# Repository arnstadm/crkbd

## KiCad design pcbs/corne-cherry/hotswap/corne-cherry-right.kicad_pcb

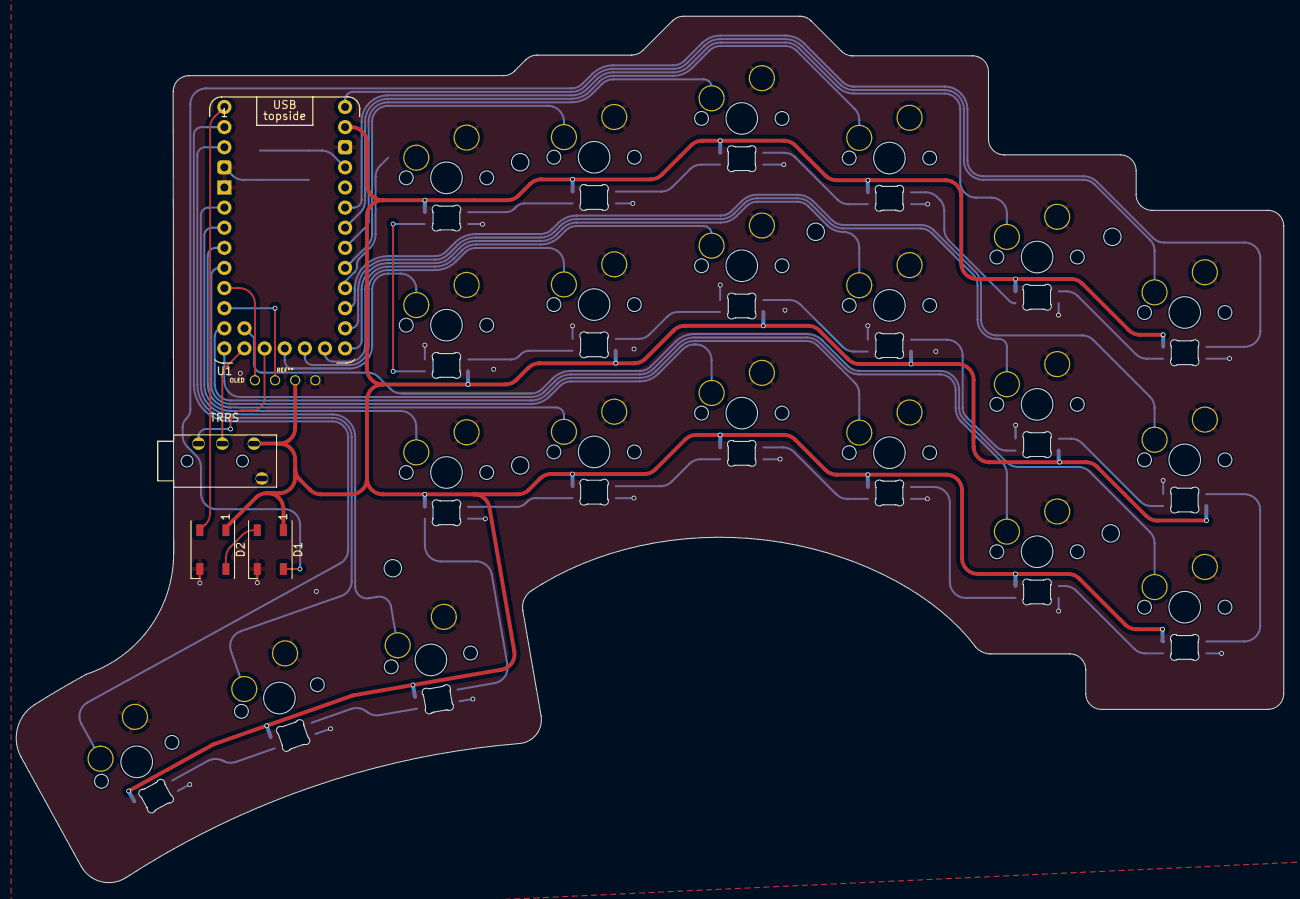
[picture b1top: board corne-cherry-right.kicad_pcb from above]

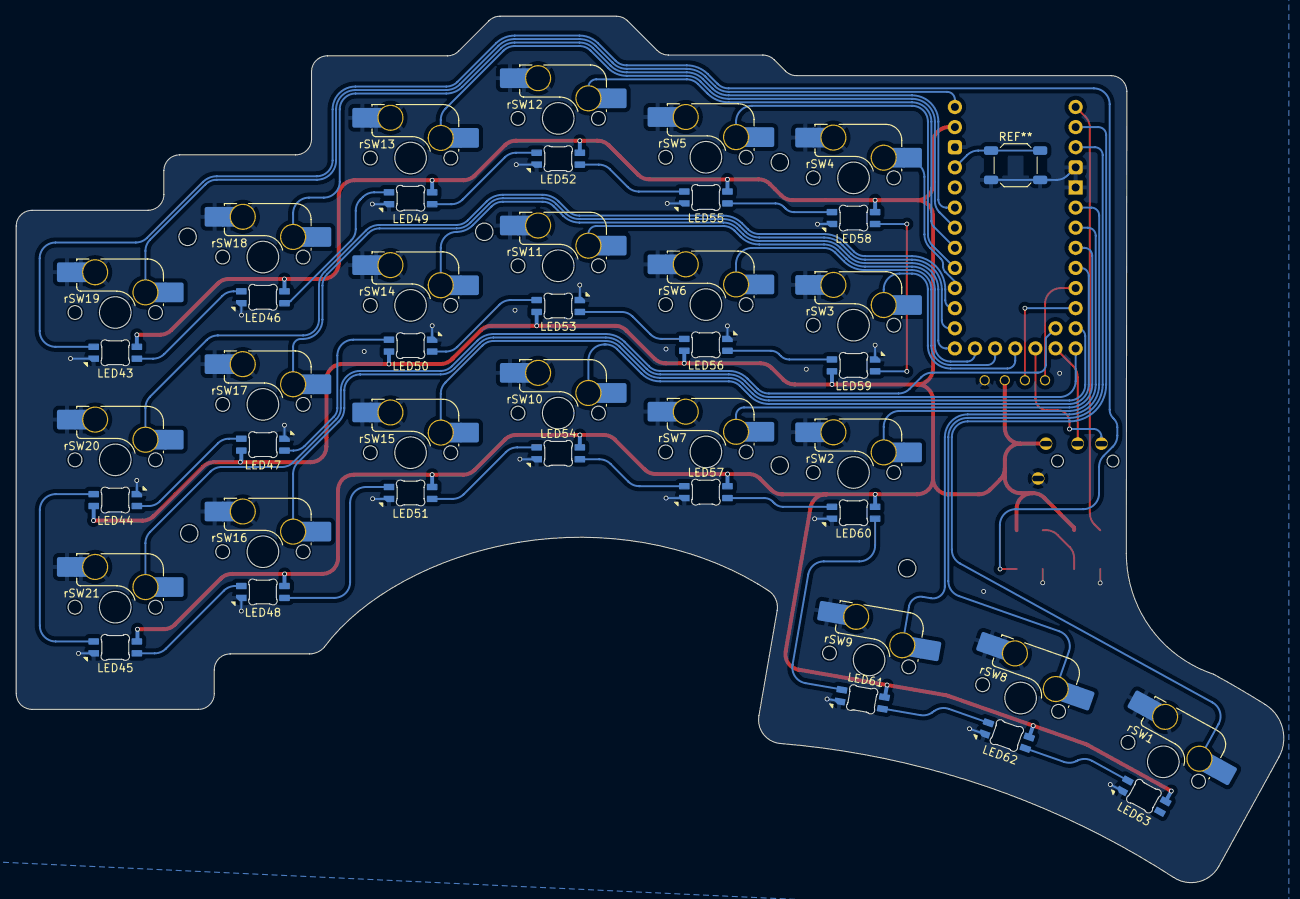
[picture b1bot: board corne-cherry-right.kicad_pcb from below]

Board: 2 copper layers, 160.0 x 109.4 mm, 47 parts (42 on the bottom side), 50 nets.

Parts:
D1, D2: WS2812B; LED_WS2812B_PLCC4_5.0x5.0mm_P3.2mm
LED43, LED45, LED46, LED48, LED49, LED51, LED52, LED54, LED55, LED57, LED58, LED60, LED61, LED62, LED63: MX_SK6812MINI-E; LED_MX_6028R
LED44, LED47, LED50, LED53, LED56, LED59: MX_SK6812MINI-E; LED_MX_6028R-ROT
TRRS: PJ-320A
U1: rp2040; rp2040promicro
rJ3: Conn_01x04; OLED
rSW1, rSW2, rSW3, rSW4, rSW5, rSW6, rSW7, rSW8, rSW9, rSW10, rSW11, rSW12, rSW13, rSW14, rSW15, rSW16, rSW17, rSW18, rSW19, rSW20, rSW21: SW_Push; SW_MX_HS_CPG151101S11_1u

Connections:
+5VR: D1.1 (VDD), D2.1 (VDD), LED43.1 (VDD), LED44.1 (VDD), LED45.1 (VDD), LED46.1 (VDD), LED47.1 (VDD), LED48.1 (VDD), LED49.1 (VDD), LED50.1 (VDD), LED51.1 (VDD), LED52.1 (VDD), LED53.1 (VDD), LED54.1 (VDD), LED55.1 (VDD), LED56.1 (VDD), LED57.1 (VDD), LED58.1 (VDD), LED59.1 (VDD), LED60.1 (VDD), LED61.1 (VDD), LED62.1 (VDD), LED63.1 (VDD), TRRS.2, U1.5V, rJ3.3
/right/KEY1: U1.0 (GP0), rSW1.1
/right/KEY2: U1.3 (GP3), rSW2.1
/right/KEY3: U1.14 (GP14), rSW3.1
/right/KEY4: U1.22 (GP22), rSW4.1
/right/KEY5: U1.26 (GP26), rSW5.1
/right/KEY6: U1.15 (GP15), rSW6.1
/right/KEY7: U1.4 (GP4), rSW7.1
/right/KEY8: U1.1 (GP1), rSW8.1
/right/KEY9: U1.2 (GP2), rSW9.1
/right/KEY10: U1.5 (GP5), rSW10.1
/right/KEY11: U1.16 (GP16), rSW11.1
/right/KEY12: U1.27 (GP27), rSW12.1
/right/KEY13: U1.28 (GP28), rSW13.1
/right/KEY14: U1.21 (GP21), rSW14.1
/right/KEY15: U1.8 (GP8), rSW15.1
/right/KEY16: U1.9 (GP9), rSW16.1
/right/KEY17: U1.23 (GP23), rSW17.1
/right/KEY18: U1.29 (GP29), rSW18.1
/right/KEY19: U1.11 (GP11), rSW19.1
/right/KEY20: U1.20 (GP20), rSW20.1
/right/KEY21: U1.25 (GP25), rSW21.1
/right/LED: D2.2 (DOUT), U1.10 (GP10)
/right/RX: TRRS.4, U1.13 (GP13)
/right/SCL: U1.7 (GP7), rJ3.2
/right/SDA: U1.6 (GP6), rJ3.1
/right/TX: TRRS.3, U1.12 (GP12)
GNDR: D1.3 (VSS), D2.3 (VSS), LED43.4 (VSS), LED44.4 (VSS), LED45.4 (VSS), LED46.4 (VSS), LED47.4 (VSS), LED48.4 (VSS), LED49.4 (VSS), LED50.4 (VSS), LED51.4 (VSS), LED52.4 (VSS), LED53.4 (VSS), LED54.4 (VSS), LED55.4 (VSS), LED56.4 (VSS), LED57.4 (VSS), LED58.4 (VSS), LED59.4 (VSS), LED60.4 (VSS), LED61.4 (VSS), LED62.4 (VSS), LED63.4 (VSS), TRRS.1, U1.G (GND), rJ3.4, rSW1.2, rSW2.2, rSW3.2, rSW4.2, rSW5.2, rSW6.2, rSW7.2, rSW8.2, rSW9.2, rSW10.2, rSW11.2, rSW12.2, rSW13.2, rSW14.2, rSW15.2, rSW16.2, rSW17.2, rSW18.2, rSW19.2, rSW20.2, rSW21.2
unnamed: D1.4 (DIN), LED43.3 (DIN)
unnamed: D1.2 (DOUT), D2.4 (DIN)
unnamed: LED43.2 (DOUT), LED46.3 (DIN)
unnamed: LED44.3 (DIN), LED47.2 (DOUT)
unnamed: LED44.2 (DOUT), LED45.3 (DIN)
unnamed: LED45.2 (DOUT), LED48.3 (DIN)
unnamed: LED46.2 (DOUT), LED49.3 (DIN)
unnamed: LED47.3 (DIN), LED50.2 (DOUT)
unnamed: LED48.2 (DOUT), LED51.3 (DIN)
unnamed: LED49.2 (DOUT), LED52.3 (DIN)
unnamed: LED50.3 (DIN), LED53.2 (DOUT)
unnamed: LED51.2 (DOUT), LED54.3 (DIN)
unnamed: LED52.2 (DOUT), LED55.3 (DIN)
unnamed: LED53.3 (DIN), LED56.2 (DOUT)
unnamed: LED54.2 (DOUT), LED57.3 (DIN)
unnamed: LED55.2 (DOUT), LED58.3 (DIN)
unnamed: LED56.3 (DIN), LED59.2 (DOUT)
unnamed: LED57.2 (DOUT), LED60.3 (DIN)
unnamed: LED58.2 (DOUT), LED59.3 (DIN)
unnamed: LED60.2 (DOUT), LED61.3 (DIN)
unnamed: LED61.2 (DOUT), LED62.3 (DIN)
unnamed: LED62.2 (DOUT), LED63.3 (DIN)

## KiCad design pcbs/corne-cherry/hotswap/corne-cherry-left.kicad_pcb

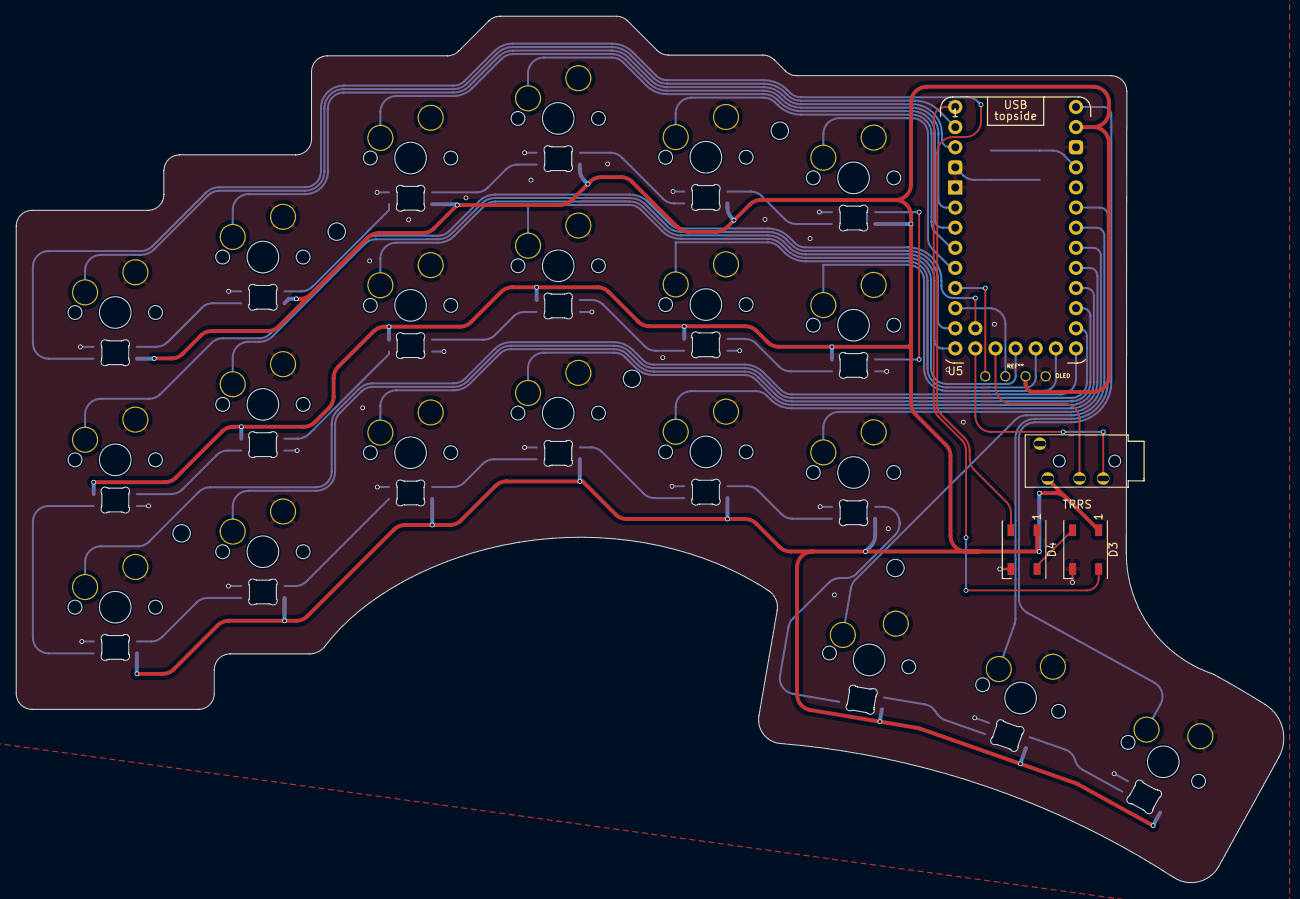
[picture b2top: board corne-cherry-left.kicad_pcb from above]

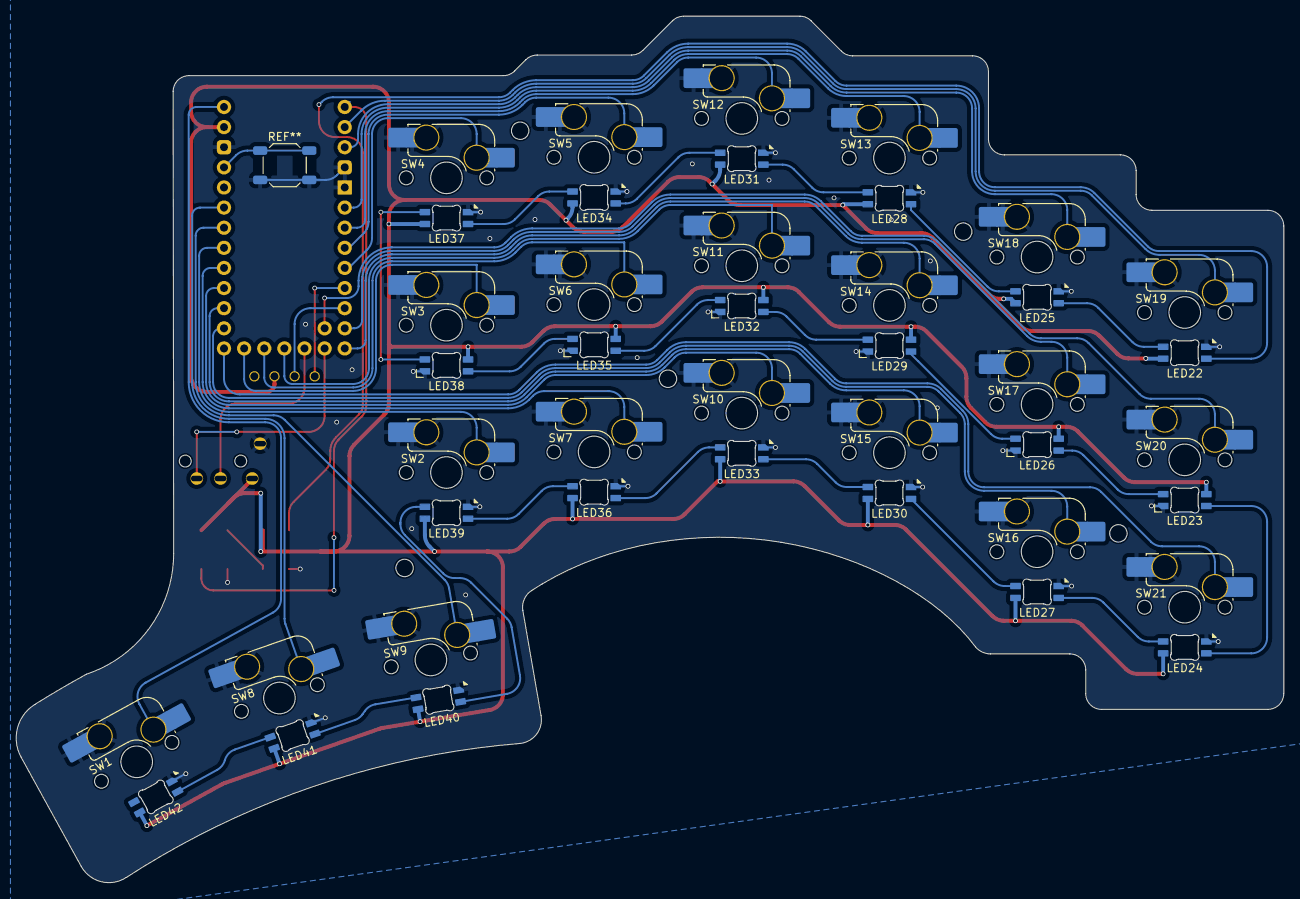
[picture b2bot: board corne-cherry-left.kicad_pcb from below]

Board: 2 copper layers, 160.0 x 109.4 mm, 47 parts (42 on the bottom side), 50 nets.

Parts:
D3, D4: WS2812B; LED_WS2812B_PLCC4_5.0x5.0mm_P3.2mm
J3: Conn_01x04; OLED
LED22, LED24, LED25, LED27, LED28, LED30, LED31, LED33, LED34, LED36, LED37, LED39, LED40, LED41, LED42: MX_SK6812MINI-E; LED_MX_6028R-ROT
LED23, LED26, LED29, LED32, LED35, LED38: MX_SK6812MINI-E; LED_MX_6028R
SW1, SW2, SW3, SW4, SW5, SW6, SW7, SW8, SW9, SW10, SW11, SW12, SW13, SW14, SW15, SW16, SW17, SW18, SW19, SW20, SW21: SW_Push; SW_MX_HS_CPG151101S11_1u
TRRS: PJ-320A
U5: rp2040; rp2040promicro

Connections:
+5V: D3.1 (VDD), D4.1 (VDD), J3.3, LED22.1 (VDD), LED23.1 (VDD), LED24.1 (VDD), LED25.1 (VDD), LED26.1 (VDD), LED27.1 (VDD), LED28.1 (VDD), LED29.1 (VDD), LED30.1 (VDD), LED31.1 (VDD), LED32.1 (VDD), LED33.1 (VDD), LED34.1 (VDD), LED35.1 (VDD), LED36.1 (VDD), LED37.1 (VDD), LED38.1 (VDD), LED39.1 (VDD), LED40.1 (VDD), LED41.1 (VDD), LED42.1 (VDD), TRRS.2, U5.5V
/left/KEY1: SW1.1, U5.11 (GP11)
/left/KEY2: SW2.1, U5.27 (GP27)
/left/KEY3: SW3.1, U5.16 (GP16)
/left/KEY4: SW4.1, U5.5 (GP5)
/left/KEY5: SW5.1, U5.4 (GP4)
/left/KEY6: SW6.1, U5.15 (GP15)
/left/KEY7: SW7.1, U5.26 (GP26)
/left/KEY8: SW8.1, U5.29 (GP29)
/left/KEY9: SW9.1, U5.28 (GP28)
/left/KEY10: SW10.1, U5.22 (GP22)
/left/KEY11: SW11.1, U5.14 (GP14)
/left/KEY12: SW12.1, U5.3 (GP3)
/left/KEY13: SW13.1, U5.2 (GP2)
/left/KEY14: SW14.1, U5.9 (GP9)
/left/KEY15: SW15.1, U5.20 (GP20)
/left/KEY16: SW16.1, U5.23 (GP23)
/left/KEY17: SW17.1, U5.8 (GP8)
/left/KEY18: SW18.1, U5.1 (GP1)
/left/KEY19: SW19.1, U5.0 (GP0)
/left/KEY20: SW20.1, U5.25 (GP25)
/left/KEY21: SW21.1, U5.21 (GP21)
/left/LED: D3.4 (DIN), U5.10 (GP10)
/left/RX: TRRS.3, U5.13 (GP13)
/left/SCL: J3.2, U5.7 (GP7)
/left/SDA: J3.1, U5.6 (GP6)
/left/TX: TRRS.4, U5.12 (GP12)
GND: D3.3 (VSS), D4.3 (VSS), J3.4, LED22.4 (VSS), LED23.4 (VSS), LED24.4 (VSS), LED25.4 (VSS), LED26.4 (VSS), LED27.4 (VSS), LED28.4 (VSS), LED29.4 (VSS), LED30.4 (VSS), LED31.4 (VSS), LED32.4 (VSS), LED33.4 (VSS), LED34.4 (VSS), LED35.4 (VSS), LED36.4 (VSS), LED37.4 (VSS), LED38.4 (VSS), LED39.4 (VSS), LED40.4 (VSS), LED41.4 (VSS), LED42.4 (VSS), SW1.2, SW2.2, SW3.2, SW4.2, SW5.2, SW6.2, SW7.2, SW8.2, SW9.2, SW10.2, SW11.2, SW12.2, SW13.2, SW14.2, SW15.2, SW16.2, SW17.2, SW18.2, SW19.2, SW20.2, SW21.2, TRRS.1, U5.G (GND)
unnamed: D3.2 (DOUT), D4.4 (DIN)
unnamed: D4.2 (DOUT), LED22.3 (DIN)
unnamed: LED22.2 (DOUT), LED25.3 (DIN)
unnamed: LED23.3 (DIN), LED26.2 (DOUT)
unnamed: LED23.2 (DOUT), LED24.3 (DIN)
unnamed: LED24.2 (DOUT), LED27.3 (DIN)
unnamed: LED25.2 (DOUT), LED28.3 (DIN)
unnamed: LED26.3 (DIN), LED29.2 (DOUT)
unnamed: LED27.2 (DOUT), LED30.3 (DIN)
unnamed: LED28.2 (DOUT), LED31.3 (DIN)
unnamed: LED29.3 (DIN), LED32.2 (DOUT)
unnamed: LED30.2 (DOUT), LED33.3 (DIN)
unnamed: LED31.2 (DOUT), LED34.3 (DIN)
unnamed: LED32.3 (DIN), LED35.2 (DOUT)
unnamed: LED33.2 (DOUT), LED36.3 (DIN)
unnamed: LED34.2 (DOUT), LED37.3 (DIN)
unnamed: LED35.3 (DIN), LED38.2 (DOUT)
unnamed: LED36.2 (DOUT), LED39.3 (DIN)
unnamed: LED37.2 (DOUT), LED38.3 (DIN)
unnamed: LED39.2 (DOUT), LED40.3 (DIN)
unnamed: LED40.2 (DOUT), LED41.3 (DIN)
unnamed: LED41.2 (DOUT), LED42.3 (DIN)

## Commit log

2024-04-27 upload of pcb
2024-04-29 split into left and right
2024-04-29 added zip files for prod
2024-05-09 add skqg
